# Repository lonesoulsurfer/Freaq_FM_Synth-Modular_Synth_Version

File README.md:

# Freaq_FM_Synth-Modular_Synth_Version

UPDATE: I have updated the original Freq Code so it now works on the current Mozzi Library.  You can find this updated code in the 'Freaq_Updated_Code' file.  I don't believe that there is any difference in sound quality and it is exactkly the same as the original which I have also included.  Both files can be found in the 'Frea_IDE_Code' folder

 The awesome Freaq FM Synth by MeeBleeps - designed for Eurorack Synths

Youtube Vid - https://www.youtube.com/watch?v=fAgmykZD0DI&source_ve_path=Mjg2NjY

First and foremost - I need to do a huge shoutout to MeeBleeps who designed this amazing synth! - https://github.com/Meebleeps/MeeBleeps-Freaq-FM-Synth

My contribution has been the design of a PCB and front panel to suit a Eurorack to suit modular synth builds.  It can be run from 12V power supply via a power connector used on on Euroracks or a 9V power supply via a JST connector.

It also can be used as a standalone synth and hand on heart, holds up to most mini synths you can buy.

The main goal with building this module is to create my own 'simple to build' modular synth. I wanted to keep everything as easy as possble with each module built with the following aims:

 - Can be powered by 9V (and 12V)
 - Easy to build with minimum components
 - Use Arduino to keep it simple (plus it helps to keep the components down and everything in tune)
 - Can fit into any modular synth Eurorck (include the ability to power the module via normal module power sources)
 - Has to sound great!

I've created a step by step guide on my Instructables page which you can find below.  This goes through how to upload the sketch using the correct version of Mozzie (1.1.2).  
https://www.instructables.com/Freaq-FM-Synth/

The Freaq FM Synth features dual independent 2-operator FM voices paired with a 2-track generative sequencer. You can stack the voices so they are in unison or have them in different polymeric step-counts. This allows you to have one voice play bass and the other lead.

This is one funky little machine! There are a tonne of controls and waveforms along with attack/delay envelope and LFO per voice.

Full instructions can be found in the Github repository

NOTE - the default start-up on the Freaq has mutation and density very low which means you might only hear a couple bleeps and boops and not much else.  To get the synth going just turn the mutation knob fully left then fully right.  Then hold down the FUNC button and do the same thing again.  This will reset the mutation & density and you'll be good to go.

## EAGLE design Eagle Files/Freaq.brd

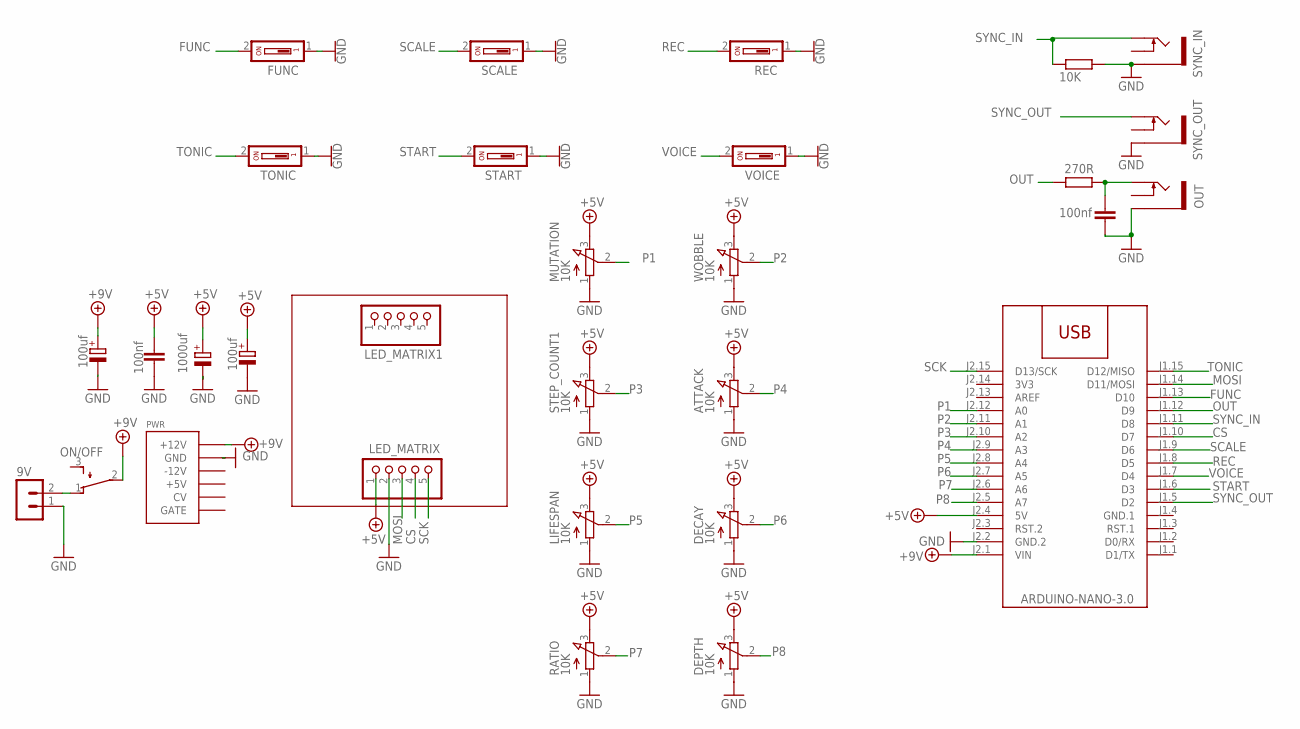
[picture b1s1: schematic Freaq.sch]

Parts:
9V: B2B-PH-K-S
ATTACK: 10K; EVUFXL
C1, C4: 100nf; C050-024X044
C2, C3: 100uf; E2-5
C5: 1000uf; E2,5-6E
DECAY: 10K; EVUFXL
DEPTH: 10K; EVUFXL
FUNC: DS01; DS-01
LED_MATRIX, LED_MATRIX1: PINHD-1X5; 1X05
LIFESPAN: 10K; EVUFXL
M1: ARDUINO-NANO-3.0
MUTATION: 10K; EVUFXL
ON/OFF: TL32PO; TL3XPO
OUT: THONKICONNNEW; WQP-PJ301M-12_JACK
PWR: POWER; POWER_16
R7: 10K; 0207/10
R8: 270R; 0207/10
RATIO: 10K; EVUFXL
REC: DS01; DS-01
SCALE: DS01; DS-01
START: DS01; DS-01
STEP_COUNT1: 10K; EVUFXL
SYNC_IN: THONKICONNNEW; WQP-PJ301M-12_JACK
SYNC_OUT: THONKICONNNEW; WQP-PJ301M-12_JACK
TONIC: DS01; DS-01
VOICE: DS01; DS-01
WOBBLE: 10K; EVUFXL

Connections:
3V3: M1.J2.14 (3V3)
+5V: ATTACK.3 (E), C1.1, C2.+, C5.+, DECAY.3 (E), DEPTH.3 (E), LED_MATRIX.1, LIFESPAN.3 (E), M1.J2.4 (5V), MUTATION.3 (E), RATIO.3 (E), STEP_COUNT1.3 (E), WOBBLE.3 (E)
+9V: C3.+, M1.J2.1 (VIN), ON/OFF.2, PWR.9 (+12V), PWR.10 (+12V)
CS: LED_MATRIX.4, M1.J1.10 (D7)
FUNC: FUNC.2, M1.J1.13 (D10)
GND: 9V.1, ATTACK.1 (A), C1.2, C2.-, C3.-, C4.2, C5.-, DECAY.1 (A), DEPTH.1 (A), FUNC.1, LED_MATRIX.2, LIFESPAN.1 (A), M1.J2.2 (GND.2), MUTATION.1 (A), OUT.P$3_SLEEVE (SLEEVE), PWR.3 (GND), PWR.4 (GND), PWR.5 (GND), PWR.6 (GND), PWR.7 (GND), PWR.8 (GND), R7.2, RATIO.1 (A), REC.1, SCALE.1, START.1, STEP_COUNT1.1 (A), SYNC_IN.P$3_SLEEVE (SLEEVE), SYNC_OUT.P$3_SLEEVE (SLEEVE), TONIC.1, VOICE.1, WOBBLE.1 (A)
GND.1: M1.J1.4 (GND.1)
MOSI: LED_MATRIX.3, M1.J1.14 (D11/MOSI)
unnamed: 9V.2, ON/OFF.1 (O)
unnamed: C4.1, OUT.P$1_TIP (TIP), R8.2
OUT: M1.J1.12 (D9), R8.1
P1: M1.J2.12 (A0), MUTATION.2 (S)
P2: M1.J2.11 (A1), WOBBLE.2 (S)
P3: M1.J2.10 (A2), STEP_COUNT1.2 (S)
P4: ATTACK.2 (S), M1.J2.9 (A3)
P5: LIFESPAN.2 (S), M1.J2.8 (A4)
P6: DECAY.2 (S), M1.J2.7 (A5)
P7: M1.J2.6 (A6), RATIO.2 (S)
P8: DEPTH.2 (S), M1.J2.5 (A7)
REC: M1.J1.8 (D5), REC.2
SCALE: M1.J1.9 (D6), SCALE.2
SCK: LED_MATRIX.5, M1.J2.15 (D13/SCK)
START: M1.J1.6 (D3), START.2
SYNC_IN: M1.J1.11 (D8), R7.1, SYNC_IN.P$1_TIP (TIP)
SYNC_OUT: M1.J1.5 (D2), SYNC_OUT.P$1_TIP (TIP)
TONIC: M1.J1.15 (D12/MISO), TONIC.2
VOICE: M1.J1.7 (D4), VOICE.2

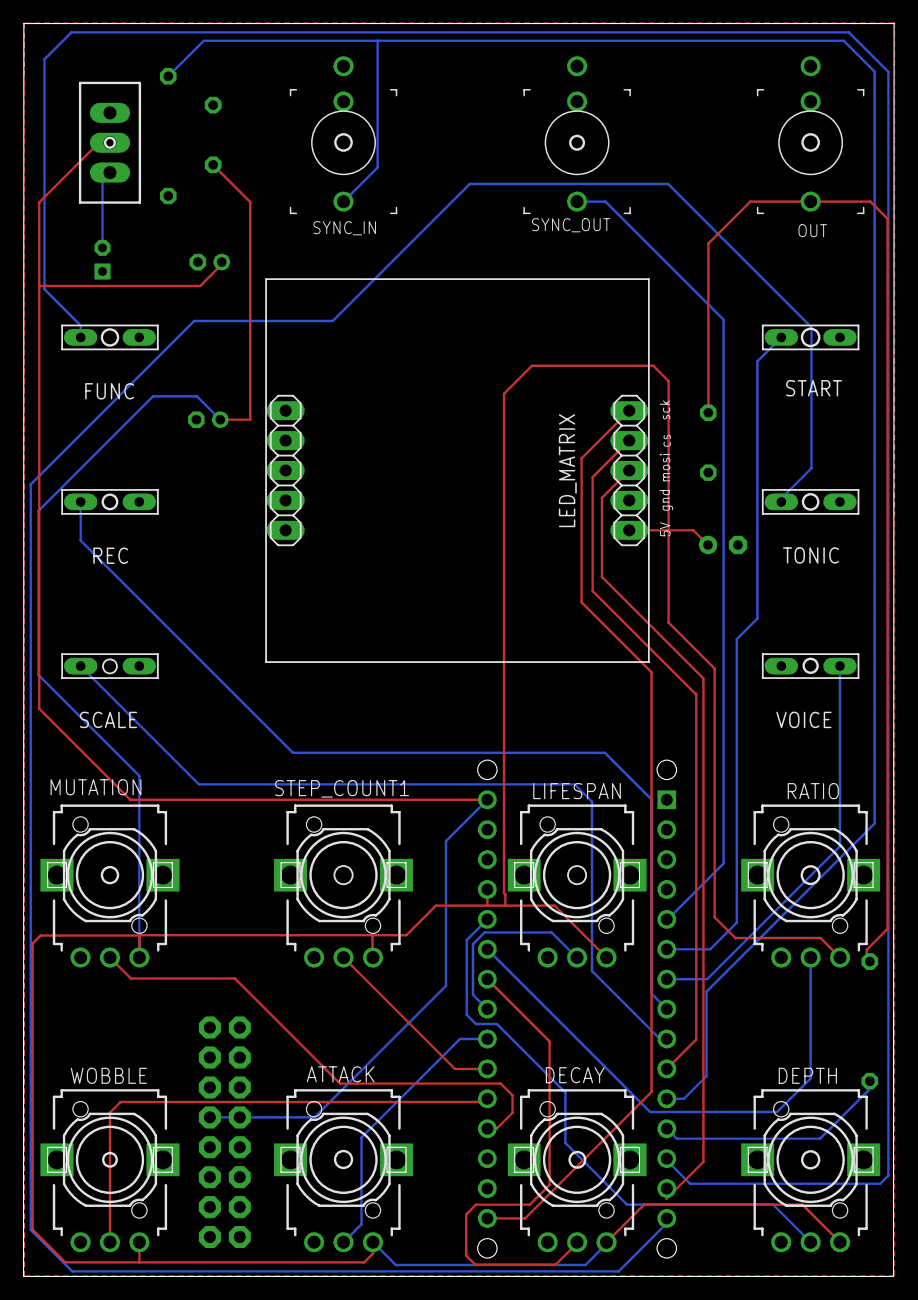
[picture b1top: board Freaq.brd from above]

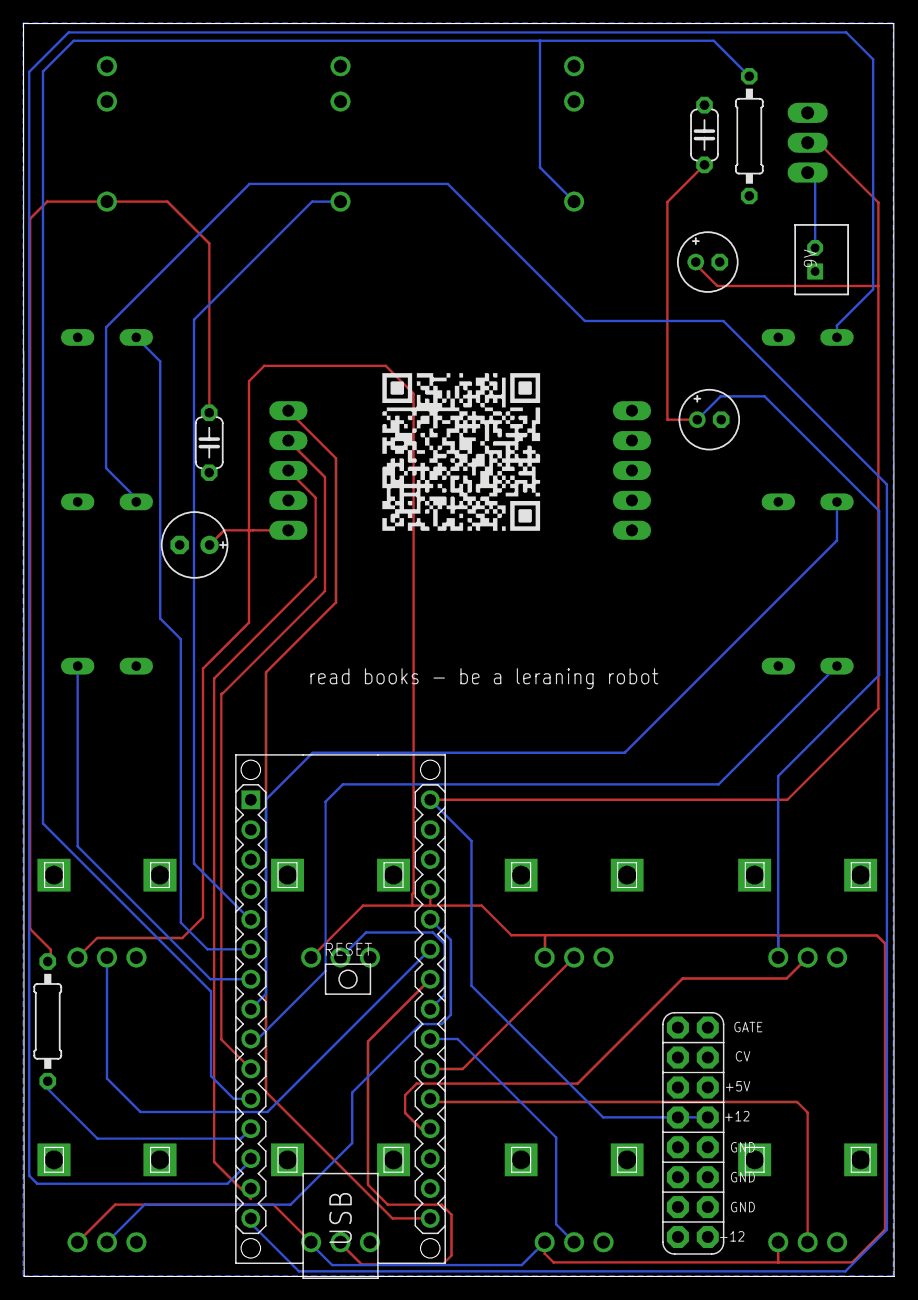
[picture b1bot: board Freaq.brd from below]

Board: 2 copper layers, 73.9 x 106.4 mm, 30 parts (10 on the bottom side), 25 nets.

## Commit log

2024-12-01 Files
2025-05-07 updated Gerber File
2025-12-22 added gerber for front panel as modified for allpcb
2025-12-22 Added additional README with tips and images
2025-12-22 Add case recommendation
    Added information about a compatible case for the project.
2025-12-29 updated code
    increase the volume and made Mutation & Density start up fully on

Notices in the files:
parts and their libraries:
diy-modules: Released under the Creative Commons Attribution 4.0 International License: http://creativecommons.org/licenses/by/4.0
SparkFun-PowerSymbols: Licensing: Creative Commons ShareAlike 4.0 International - https://creativecommons.org/licenses/by-sa/4.0
